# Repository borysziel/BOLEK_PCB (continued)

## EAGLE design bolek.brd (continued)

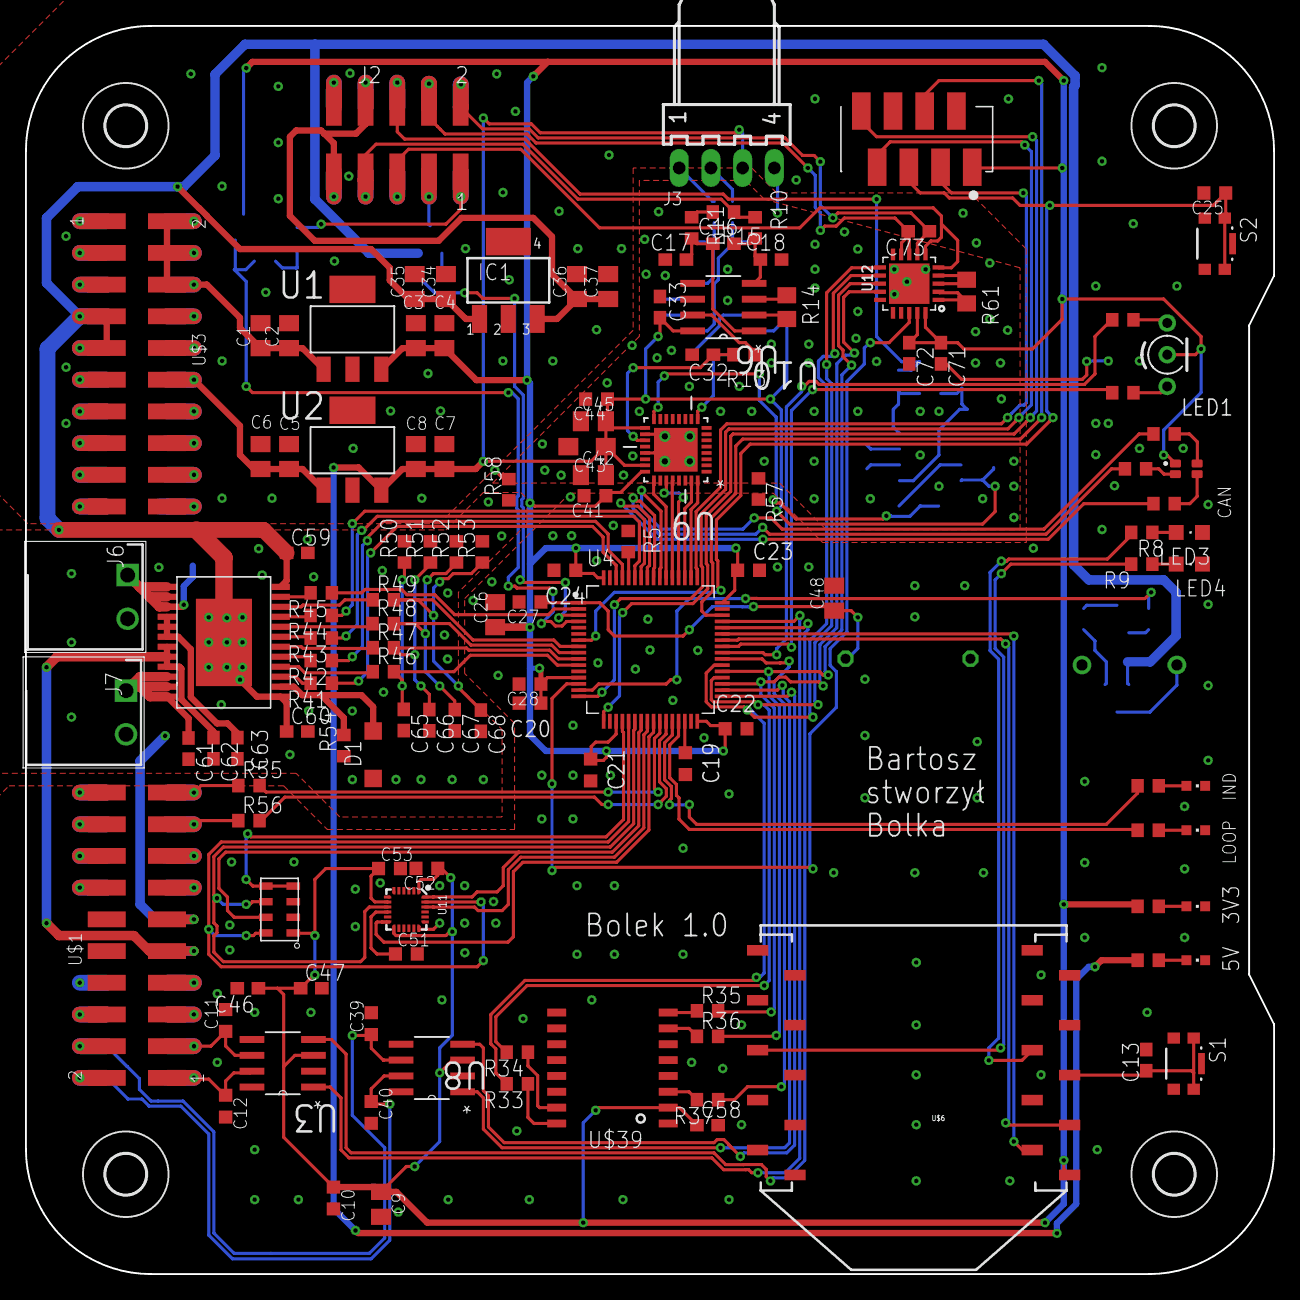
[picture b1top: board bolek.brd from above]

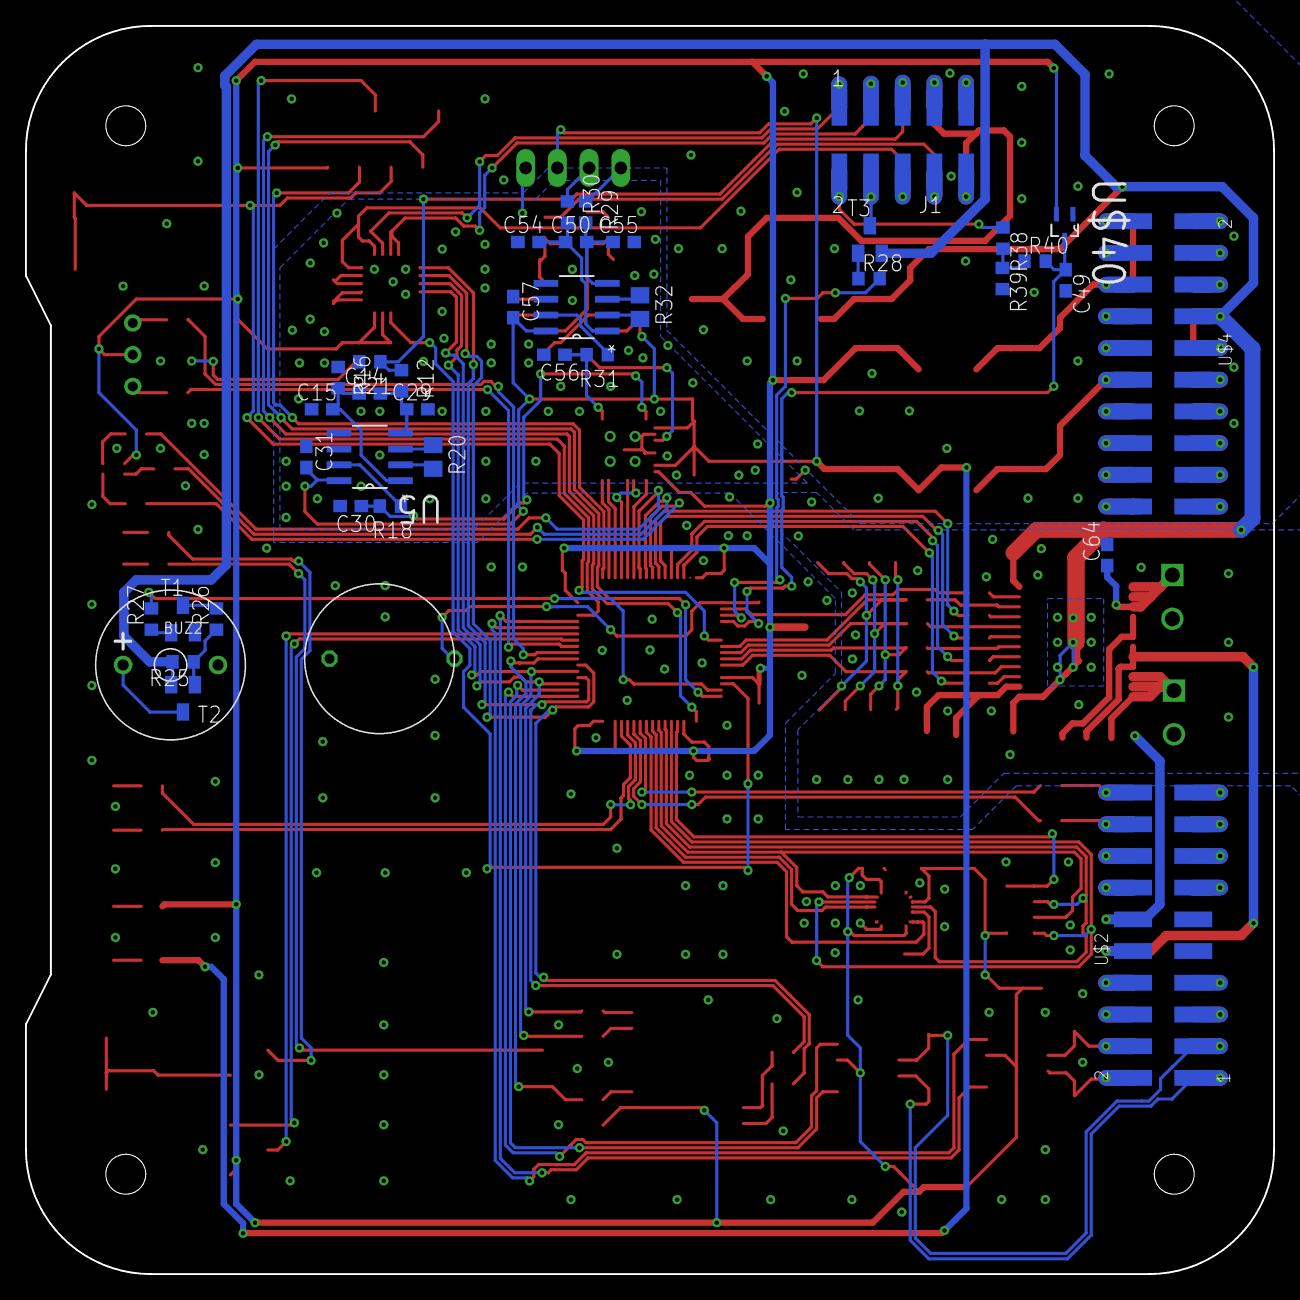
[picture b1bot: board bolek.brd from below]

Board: 2 copper layers, 100.0 x 100.0 mm, 174 parts (39 on the bottom side), 149 nets.

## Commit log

2019-08-27 last version
